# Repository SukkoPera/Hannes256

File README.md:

# Hannes256
Hannes256 is an Open Hardware internal 256 kB RAM Expansion board for the Commodore 16.

## Summary
A long time ago, a Plus/4 hacker named [Hannes](https://plus4world.powweb.com/profile/Hannes) devised a way to use more than 64 kB of RAM on the machine. Together with [Solder](https://plus4world.powweb.com/members/Solder) they published [some notes](http://www.solder-synergy.de/plus4/hardware/makers/ram256kb.zip) in order to allow every Plus/4 owner to do the modification on their machines.

Unfortunately the modification is quite long and complex, requiring chips to be replaced, others to be added ("piggybacked"), lots of wires to be soldered and even some tracks to be cut. This is almost unavoidable on the Plus/4 due to the little space available inside the machine, but Commodore 16 owners have more luck in this regard. So I started from Solder's notes, figured out the logic behind it and reimplemented everything in a single board that can be sandwiched between the TED and its socket.

A 256 kB Hannes-style RAM expansion is first of all a standard 64 kB RAM expansion, so your C16 will immediately gain compatibility with all the software developed for the Plus/4, while also being able to run any software that requires 256 kB.

Hannes256 works by redirecting all RAM accesses to onboard chips, therefore it can also be used to repair mainboards with failed RAM chips and/or multiplexers.

If for any reason you want to go back to 16 kB, just toggle the J2 jumper: Hannes256 will be deactivated and the mainboard RAM will be back in business.

## Design and Assembly Notes
This project uses some SMD components due to space constraints, you are recommended to solder those first.

U5 and U6 can either be 74x157 or 74x257, as they are permanently enabled. I recommend using chips from the HCT family, but LS will do. Do NOT use HC.

Be careful with U3 and U4: these chips come in different widths. The board is made for 5.30 mm wide chips (which are the ones indicated in the BOM), you can probably fit wider ones but you are on your own.

The actual 41256 RAM chips have been out of production for ages but they can still be bought on AliExpress & similar sites.

You can connect a switch to U2 if you want to be able to switch back to 16 kB without having to open the case again. Honestly I just wouldn't bother, there is virtually no software that requires no more than 16 kB and it should just be fixed if this is really the case.

The board was accurately sized to fit alongside the CPU in a C16, but if you are using a CPU replacement it might just not physically fit. The same applies if you are using a Commodore 116, on which the board is not tested but it should theoretically work. I am sorry for that, feel free to redesign it and adjust the shape accordingly, it's easy to do with open source hardware.

Finally, U2 can either be a GAL20 or a GAL22: the former you can buy cheaply from AliExpress while the latter can be found new made by Atmel (ATF22-whatever). Whichever you choose, make sure to program it with the corresponding file from the [gal directory](gal/).

### RAM Compatibility
I have used NEC D41256C-15 chips for my own testing. These have 150 ns access time which is probably as slow as you can go (The TED architecture should work even with 200 ns but I doubt you will find any RAMs that are that slow). This probably means that many other - if not all - 256k x 1 RAMs will work.

## Installation
The board needs 3 wires from J3 to be connected to some points on the mainboard. You can either solder them or use clips and perform a fully solderless installation.

### Commodore 16:
* `CS_OUT` must be connected to pin 10 of U11.
* `CS_IN` must be connected to the **LIFTED** pin 16 of U16: remove the chip from the socket and carefully bend pin 16 so that it no longer gets inserted into the socket, then reinsert the chip and connect the clip to the now-dangling pin.
* `RESET` must be connected to pin 2 of U9 or to pin 40 of U2, whichever is easier for you.

See [here](img/installation.jpg) for an explanatory picture.

### Plus/4
Installation on the Plus/4 is much trickier, due to the very little space available, but it can still be carried out, if you are handy enough to do some work inside the machine:
1. Completely remove the metal shield around the TED chip.
2. Remove the TED socket.
3. Unsolder transistor Q2 and [move it further to the left using wires](img/plus4_installation_2.jpeg).
4. Remove the 10uF capacitor, replace it with a new one with longer legs and [move it further to the right](img/plus4_installation_1.jpeg).
5. Solder Hannes512 in place of the TED.
6. Solder the cables to the connection points:
   * `CS_OUT` must be connected to pin 19 of U5.
   * `CS_IN` must be connected to the **LIFTED** pin 16 of U19.
   * `RESET` must be connected to pin 12 of U7 or to any other convenient /RESET point.
8. Put a heatsink on the TED.
9. Add some electrical tape to the bottom of the keyboard to [insulate the two screws that would touch the board](img/plus4_installation_3.jpeg).

### Commodore 116
No idea at the moment, sorry. Please report back if you manage to carry out an installation.

## Technical Notes
The basic idea behind the Hannes-style memory expansion mechanism is to intercept the Userport /CS range ($FD10-FD1F, PLA pin 16) and further decode it, feeding $FD10 only to its original purpose and using the remaining addresses for other stuff. In particular, $FD16 (64790) will be the control register for our RAM expansion (see ioarea.txt for further address assignments).

We are bound to using 41256 (256k x 1) RAM chips, as their internal matrix is organized in 256 rows by 1024 columns and thus only need rows A0-A7 for RAS-only refresh (which is the way the TED performs DRAM refresh). 44256 chips (256k x 4) would make life easier but they are generally organized in 512 rows and would need a much more complex refresh logic, in order to refresh the pages that are currently not selected.

This board has 14 chips (!) thus it is quite likely to significantly increase the power draw of your machine. **Make sure to be using a good power supply**.

## Testing
Start with [siz's memory test program](http://siz.hu/external/memory_test.prg): it must detect the 256 kB and the full test should complete without reporting any errors.

Then you can pick something from the [Plus/4 World's 256k Support section](https://plus4world.powweb.com/effects/256K_Support): [Future World](https://plus4world.powweb.com/software/Future_World) and [Dream World](https://plus4world.powweb.com/software/Dream_World) are perfect, and [Taurin](https://plus4world.powweb.com/software/Taurin) can be also a good candidate. Be aware that these old demos might use specific loaders that are unlikely to cooperate with an SD2IEC.

Note that some software from that section requires a different expansion (i.e.: *Csory* or something else): that will not work with Hannes256.

## Programming
The expansion is controlled through a single 8-bit register at $FD16, whose individual bits control the memory configuration:
* Bit 0/1: Select RAM bank (0-3)
* Bit 2/3: Leave at 1 in order to allow compaibility with larger memory expansions
* Bit 4/5: Leave at 1 for compatibility with the expansion by CSORY
* Bit 6: "TED-feature" (added in "Update 1" of the original design):
  * 0: TED always accesses the *default* bank (see below)
  * 1: TED accesses the RAM-bank selected with bits 0 and 1
* Bit 7: Set the switch bound:
  * 0: >= $1000
  * 1: >= $4000

It should now be apparent that Hannes-style memory expansions work by allowing switching among different 64 kB banks. A 256 kB expansion thus allows for 4 banks, but only 240kB can actually be used, since memory lower than $1000 cannot be switched. A further restriction is possible through bit 7.

There is a concept of *default bank* (also called *standard bank*), which is the bank that:
* is automatically selected at power-up
* is accessed by the TED when bit 6 of the control register is cleared
* is accessed for all addresses < $1000 (or < $4000 when bit 7 of the control register is set)

This bank is indicated as bank 3 in Solder's notes, but **this might be misleading**: keep in mind that bits 2 and 3 of the control register must always be set to 1, so it's better the think of it as **bank 15**. With a 256 kB expansion this is the same bank as bank 3 but with larger expansions this would not be the case, so if you want maximum compatibility for your software, remember to **always keep bits 2 and 3 at 1**.

## Releases
If you want to get this board produced, you are recommended to get [the latest release](https://github.com/SukkoPera/Hannes256/releases) rather than the current git version, as the latter might be under development and is not guaranteed to be working.

Every release is accompanied by its Bill Of Materials (BOM) file and any relevant notes about it, which you are recommended to read carefully.

## License
The Hannes256 documentation, including the design itself, is copyright &copy; SukkoPera 2022-2023 and is licensed under the [Creative Commons Attribution-NonCommercial-ShareAlike 4.0 International License](https://creativecommons.org/licenses/by-nc-sa/4.0/).

This documentation is distributed *as is* and WITHOUT ANY EXPRESS OR IMPLIED WARRANTIES whatsoever with respect to its functionality, operability or use, including, without limitation, any implied warranties OF MERCHANTABILITY, SATISFACTORY QUALITY, FITNESS FOR A PARTICULAR PURPOSE or infringement. We expressly disclaim any liability whatsoever for any direct, indirect, consequential, incidental or special damages, including, without limitation, lost revenues, lost profits, losses resulting from business interruption or loss of data, regardless of the form of action or legal theory under which the liability may be asserted, even if advised of the possibility or likelihood of such damages.

## Support the Project
If you want to get some boards manufactured, you can get them from PCBWay through this link:

You get my gratitude and cheap, professionally-made and good quality PCBs, I get some credit that will help with this and [other projects](https://www.pcbway.com/project/member/?bmbno=72D33927-5EF6-42). You won't even have to worry about the various PCB options, it's all pre-configured for you!

Also, if you still have to register, [you can use this link](https://www.pcbway.com/setinvite.aspx?inviteid=41100) to get some bonus initial credit (and yield me some more).

You can also buy me a coffee if you want:

## Credits
* Hannes and Solder for the original design and documentation.
* Levente Hársfalvi (TLC) for plenty of help, in particular with the MOS 6529 replacement circuit.
* siz for the memory test utility.
* Arpad Darvas for coming up with the Plus/4 installation procedure and documenting it.

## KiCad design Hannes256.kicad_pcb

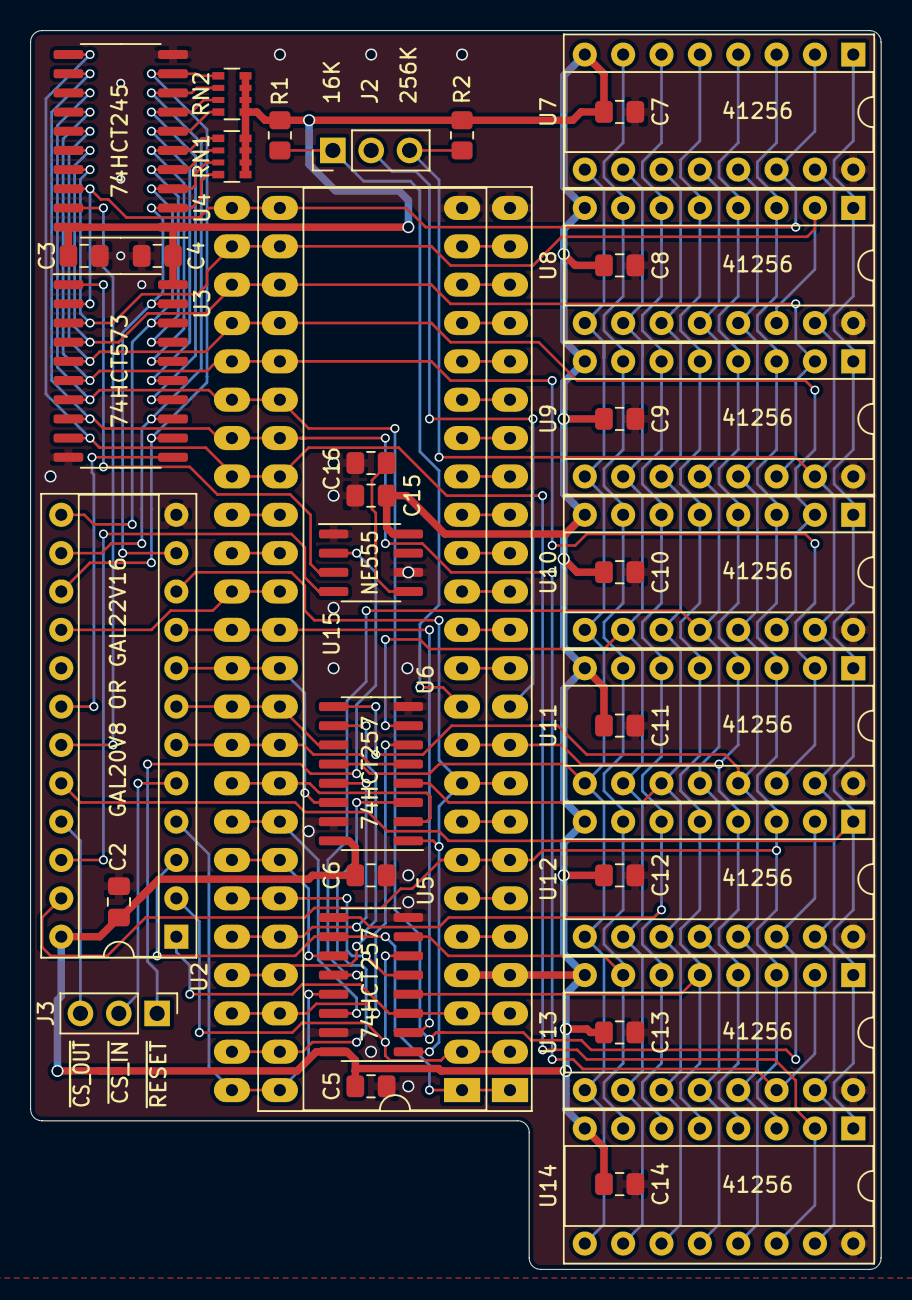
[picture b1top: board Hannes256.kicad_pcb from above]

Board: 2 copper layers, 56.3 x 82.0 mm, 38 parts (1 on the bottom side), 75 nets.

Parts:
C2, C3, C4, C5, C6, C7, C8, C9, C10, C11, C12, C13, C14, C15: 100n; C_0805_2012Metric_Pad1.18x1.45mm_HandSolder
C16: 10n; C_0805_2012Metric_Pad1.18x1.45mm_HandSolder
J1: TED_SOCKET; DIP-48_W15.24mm_LongPads_ModSilkS
J2: RAM_SELECTOR; PinHeader_1x03_P2.54mm_Vertical
J3: CONN_CS; PinHeader_1x03_P2.54mm_Vertical
R1, R2: 10k; R_0805_2012Metric_Pad1.20x1.40mm_HandSolder
RN1, RN2: 1k; R_Array_Convex_4x0603
U1: MOS_7360_TED; DIP-48_W15.24mm_Socket_LongPads
U2: GAL20V8; DIP-24_W7.62mm_Socket
U3: 74HCT573; SO-20_5.3x12.6mm_P1.27mm
U4: 74HCT245; SO-20_5.3x12.6mm_P1.27mm
U5, U6: 74HCT257; SOIC-16_3.9x9.9mm_P1.27mm
U7, U8, U9, U10, U11, U12, U13, U14: 41256; DIP-16_W7.62mm_Socket
U15: NE555; SOIC-8_3.9x4.9mm_P1.27mm
V0: CC_LOGO; cc_by_nc_sa

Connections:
+5V: C2.1, C3.1, C4.1, C5.1, C6.1, C7.1, C8.1, C9.1, C10.1, C11.1, C12.1, C13.1, C14.1, C15.1, J1.4, R1.1, R2.1, RN1.5, RN1.6, RN1.7, RN1.8, RN2.5, RN2.6, RN2.7, RN2.8, U1.4, U2.24, U3.20, U4.1, U4.20, U5.16, U6.16, U7.8, U8.8, U9.8, U10.8, U11.8, U12.8, U13.8, U14.8, U15.8
/ba: J1.34, U1.34
/clkin: J1.14, U1.14
/clkout: J1.12, U1.12
/color: J1.13, U1.13
/cs0: J1.5, U1.5
/cs1: J1.6, U1.6
/k0: J1.15, U1.15
/k1: J1.16, U1.16
/k2: J1.17, U1.17
/k3: J1.18, U1.18
/k4: J1.19, U1.19
/k5: J1.20, U1.20
/k6: J1.21, U1.21
/k7: J1.22, U1.22
/lum: J1.23, U1.23
/snd: J1.33, U1.33
/~RAS~/~CAS~ Generation/cs_ramwr: U2.18, U3.11
/~RAS~/~CAS~ Generation/~cs_ramrd: U2.19, U4.19
/~RAS~/~CAS~ Generation/~cs_ramwr: U2.22, U15.4
/~RAS~/~CAS~ Generation/~u3enable: U3.1, U15.3
/~cas: J2.2, U1.11
/~cas_16k: J1.11, J2.1, R1.2
/~irq: J1.8, U1.8
AEC: J1.35, U1.35, U2.16
GND: C2.2, C3.2, C4.2, C5.2, C6.2, C7.2, C8.2, C9.2, C10.2, C11.2, C12.2, C13.2, C14.2, C15.2, C16.2, J1.24, U1.24, U2.12, U3.10, U4.10, U5.8, U5.15, U6.8, U6.15, U7.16, U8.16, U9.16, U10.16, U11.16, U12.16, U13.16, U14.16, U15.1, U15.6
MUX: J1.9, U1.9, U2.10, U5.1, U6.1
unnamed: C16.1, U15.5
R_~W: J1.7, U1.7, U2.23, U7.3, U8.3, U9.3, U10.3, U11.3, U12.3, U13.3, U14.3
a0: J1.3, U1.3, U2.1, U5.3
a1: J1.2, U1.2, U2.2, U5.6
a2: J1.1, U1.1, U2.3, U5.10
a3: J1.48, U1.48, U2.4, U5.13
a4: J1.47, U1.47, U6.3
a5: J1.46, U1.46, U6.6
a6: J1.45, U1.45, U6.10
a7: J1.44, U1.44, U6.13
a8: J1.43, U1.43, U5.5
a9: J1.42, U1.42, U5.11
a10: J1.41, U1.41, U5.14
a11: J1.40, U1.40, U6.2
a12: J1.39, U1.39, U2.6, U6.5
a13: J1.38, U1.38, U2.7, U6.11
a14: J1.37, U1.37, U2.8, U6.14
a15: J1.36, U1.36, U2.9, U5.2
d0: J1.25, U1.25, U3.2, U4.18, U7.2, U7.14
d1: J1.26, U1.26, U3.3, U4.17, U8.2, U8.14
d2: J1.27, U1.27, U3.4, U4.16, U9.2, U9.14
d3: J1.28, U1.28, U3.5, U4.15, U10.2, U10.14
d4: J1.29, U1.29, U3.6, U4.14, U11.2, U11.14
d5: J1.30, U1.30, U3.7, U4.13, U12.2, U12.14
d6: J1.31, U1.31, U3.8, U4.12, U13.2, U13.14
d7: J1.32, U1.32, U3.9, U4.11, U14.2, U14.14
m0: U5.4, U7.5, U8.5, U9.5, U10.5, U11.5, U12.5, U13.5, U14.5
m1: U5.7, U7.7, U8.7, U9.7, U10.7, U11.7, U12.7, U13.7, U14.7
m2: U5.9, U7.6, U8.6, U9.6, U10.6, U11.6, U12.6, U13.6, U14.6
m3: U5.12, U7.12, U8.12, U9.12, U10.12, U11.12, U12.12, U13.12, U14.12
m4: U6.4, U7.11, U8.11, U9.11, U10.11, U11.11, U12.11, U13.11, U14.11
m5: U6.7, U7.10, U8.10, U9.10, U10.10, U11.10, U12.10, U13.10, U14.10
m6: U6.9, U7.13, U8.13, U9.13, U10.13, U11.13, U12.13, U13.13, U14.13
m7: U6.12, U7.9, U8.9, U9.9, U10.9, U11.9, U12.9, U13.9, U14.9
m8: U2.20, U7.1, U8.1, U9.1, U10.1, U11.1, U12.1, U13.1, U14.1
p0: RN1.4, U2.11, U3.19, U4.2
p1: RN1.3, U2.13, U3.18, U4.3
p2: RN1.2, U3.17, U4.4
p3: RN1.1, U3.16, U4.5
p4: RN2.4, U3.15, U4.6
p5: RN2.3, U3.14, U4.7
p6: RN2.2, U2.14, U3.13, U4.8
p7: RN2.1, U2.15, U3.12, U4.9
~CAS_64K: J2.3, R2.2, U7.15, U8.15, U9.15, U10.15, U11.15, U12.15, U13.15, U14.15
~CS_IN: J3.2, U2.5
~CS_OUT: J3.3, U2.21
~RAS: J1.10, U1.10, U7.4, U8.4, U9.4, U10.4, U11.4, U12.4, U13.4, U14.4
~RESET: J3.1, U15.2

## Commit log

2022-10-24 Add GAL22 files
2022-10-25 Bring R/W to the GAL We'll have to write an essay on this...
2022-10-25 Center C13 within U13 The socket won't fit otherwise!
2022-10-25 Cosmetics
2022-10-26 Only enable RAM register during writes
2022-10-29 Add a 74x245 to provide RAM register read functionality
2022-12-08 Use a different MOS 6529 replacement circuit, courtesy of TLC
2022-12-11 Update silkscreen
2023-01-09 Fix U3 Latch Enable, sigh... GAL equations TBD
2023-01-09 Update GAL equations for Latch Enable modifications
2023-03-14 Use narrower footprint for U3/U4 and move everything on the top layer
2023-03-14 Final touches
2023-12-28 Add P/Ns
2023-12-29 Add installation pictures
2023-12-30 Remove font link, that is for another board
2023-12-30 Use bank 3 when in non-switchable range *Maybe* this only reshuffles the banks around, but anyway it results in simplified equations that let us avoid using an intermediate signal, freeing one pin - 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
2023-12-30 Simplify GAL equations
2023-12-30 Typo
2026-02-13 Update coffee donation link image in README
    Updated the coffee donation link with a new image.
2026-03-30 Add installation instructions for Plus/4 and C116
    Added installation instructions for Plus/4 and Commodore 116, including detailed steps and connections.
2026-03-30 Reorganize credits and thanks sections in README
2026-03-30 Fix typo in README.md
2026-03-31 Clarify installation instructions in README

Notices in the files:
Hannes256.kicad_pcb:
Licensed under CC BY-NC-SA 4.0
